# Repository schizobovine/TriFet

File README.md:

TriFet Motor Driver
-------------------

All credit goes to [Ethan Zonca](http://protofusion.org/), who released the design as Open Source Hardware. Kudos, sir!

Original [TriFet Repository](http://protofusion.org/hg/TriFet/) (Mercurial)

This is my own bit of hacking on it to use as an alternative motor driver for Nerf guns in case my [Polulu High-Power Motor Driver 18v15 (G1)](https://www.pololu.com/product/755) ever lets out the blue smoke. It's special because the G2 drivers all include current choppers, which limits the initial enormous inrush current from the high-power, unprotected RC batteries I'm using (similar to those used in drones). With the current chopper on the VNH5019 (first driver I used), except for absurdly low PWM values, the motor would "warbble" as it kept hitting the limit, backing off, and hitting it again. The G2 custom drivers also include a similar current chopper, hence the desire to avoid it.

I'm trying to optimize for spin-up speed, as the main drawback to motorized Nerf blasters are the noise they make when the flywheels are on. While this could potentially be silenced, it would require a complete overhaul and is sorta out of the realm of a \<\$100 plastic "toy" mod. If I can get \< 1 second spin-up time, I'll probably be happy.

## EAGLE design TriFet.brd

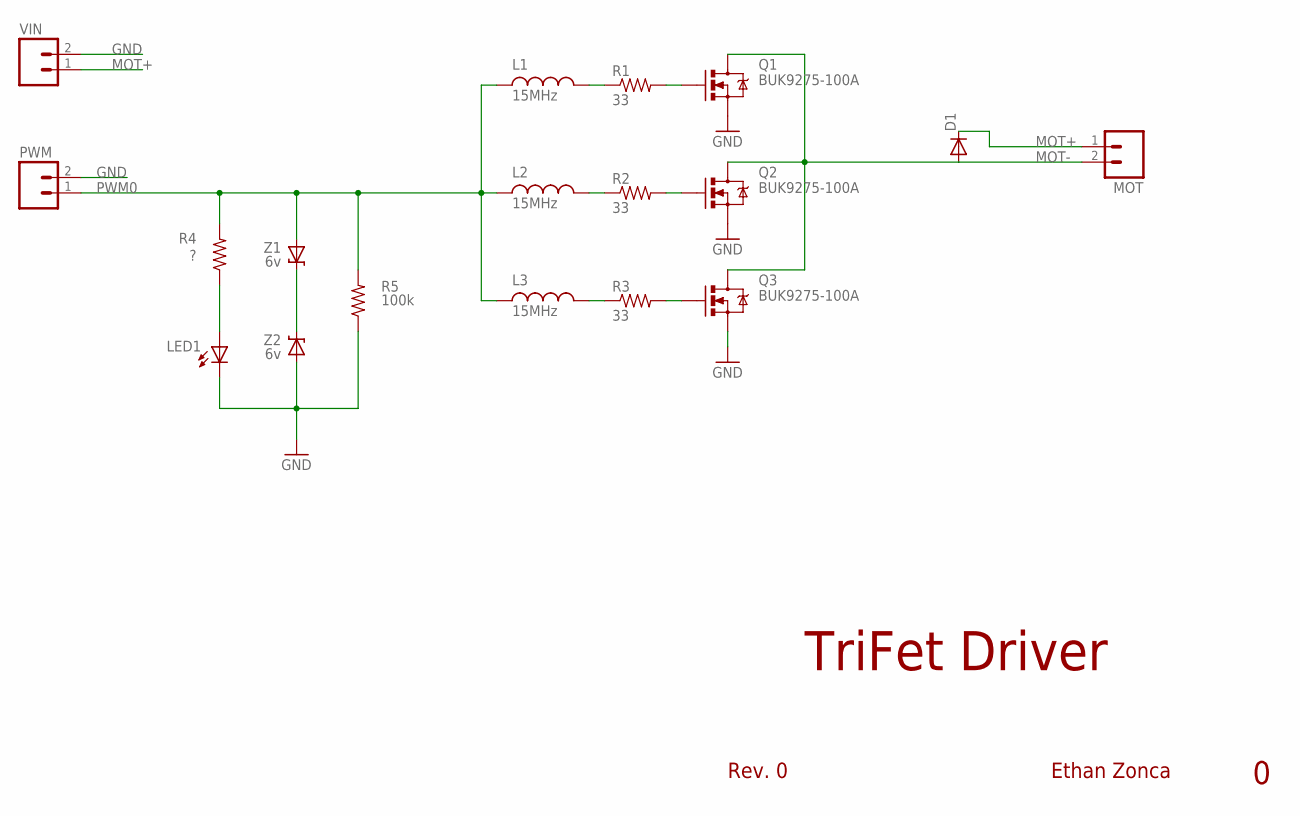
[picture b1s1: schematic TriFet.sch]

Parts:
D1: DIODESMB; SMB-DIODE
L1, L2, L3: 15MHz; 0603
LED1: LEDCHIP-LED0603; CHIP-LED0603
MOT: M023.5MM; SCREWTERMINAL-3.5MM-2
PWM: M023.5MM-NO_SILK; SCREWTERMINAL-3.5MM-2-NS
Q1, Q2, Q3: BUK9275-100A; DPAK
R1, R2, R3: 33; 0603-RES
R4: ?; 0603-RES
R5: 100k; 0603-RES
VIN: M023.5MM-NO_SILK; SCREWTERMINAL-3.5MM-2-NS
Z1, Z2: 6v; SOD-323

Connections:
GND: LED1.C, PWM.2, Q1.3 (S), Q2.3 (S), Q3.3 (S), R5.1, VIN.2, Z2.2 (A)
MOT+: D1.C, MOT.1, VIN.1
MOT-: D1.A, MOT.2, Q1.4 (D), Q2.4 (D), Q3.4 (D)
unnamed: Q1.1 (G), R1.2
unnamed: L1.2, R1.1
unnamed: LED1.A, R4.1
unnamed: L2.2, R2.1
unnamed: Q2.1 (G), R2.2
unnamed: Z1.1 (C), Z2.1 (C)
unnamed: L3.2, R3.1
unnamed: Q3.1 (G), R3.2
PWM0: L1.1, L2.1, L3.1, PWM.1, R4.2, R5.2, Z1.2 (A)

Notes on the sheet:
TriFet Driver
Rev. 0
Ethan Zonca

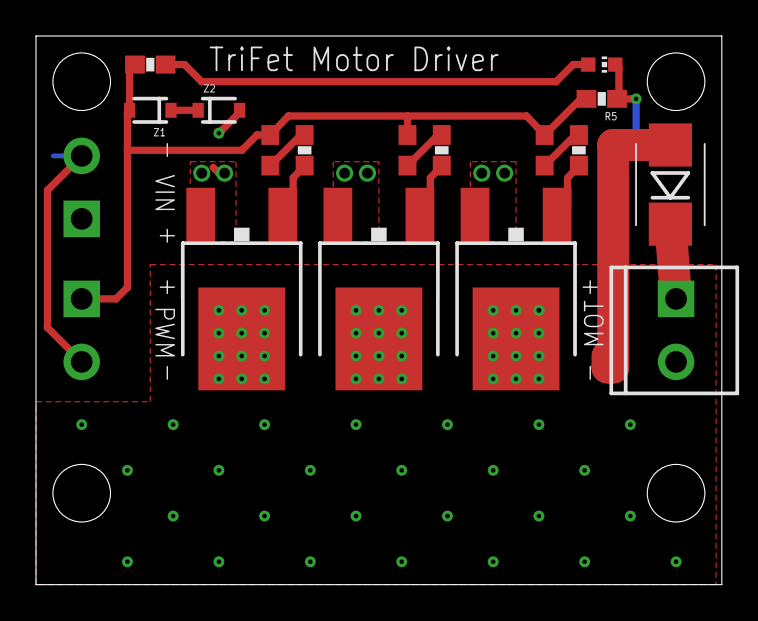
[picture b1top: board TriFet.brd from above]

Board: 2 copper layers, 38.1 x 30.5 mm, 18 parts (0 on the bottom side), 12 nets.

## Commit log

2012-12-15 Initial import
2017-12-02 adding readme and pointers back to original author for credit
2017-12-02 include images and schematic image from original author

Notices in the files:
parts and their libraries:
SparkFun: Licensing: CC v3.0 Share-Alike You are welcome to use this library for commercial purposes.
